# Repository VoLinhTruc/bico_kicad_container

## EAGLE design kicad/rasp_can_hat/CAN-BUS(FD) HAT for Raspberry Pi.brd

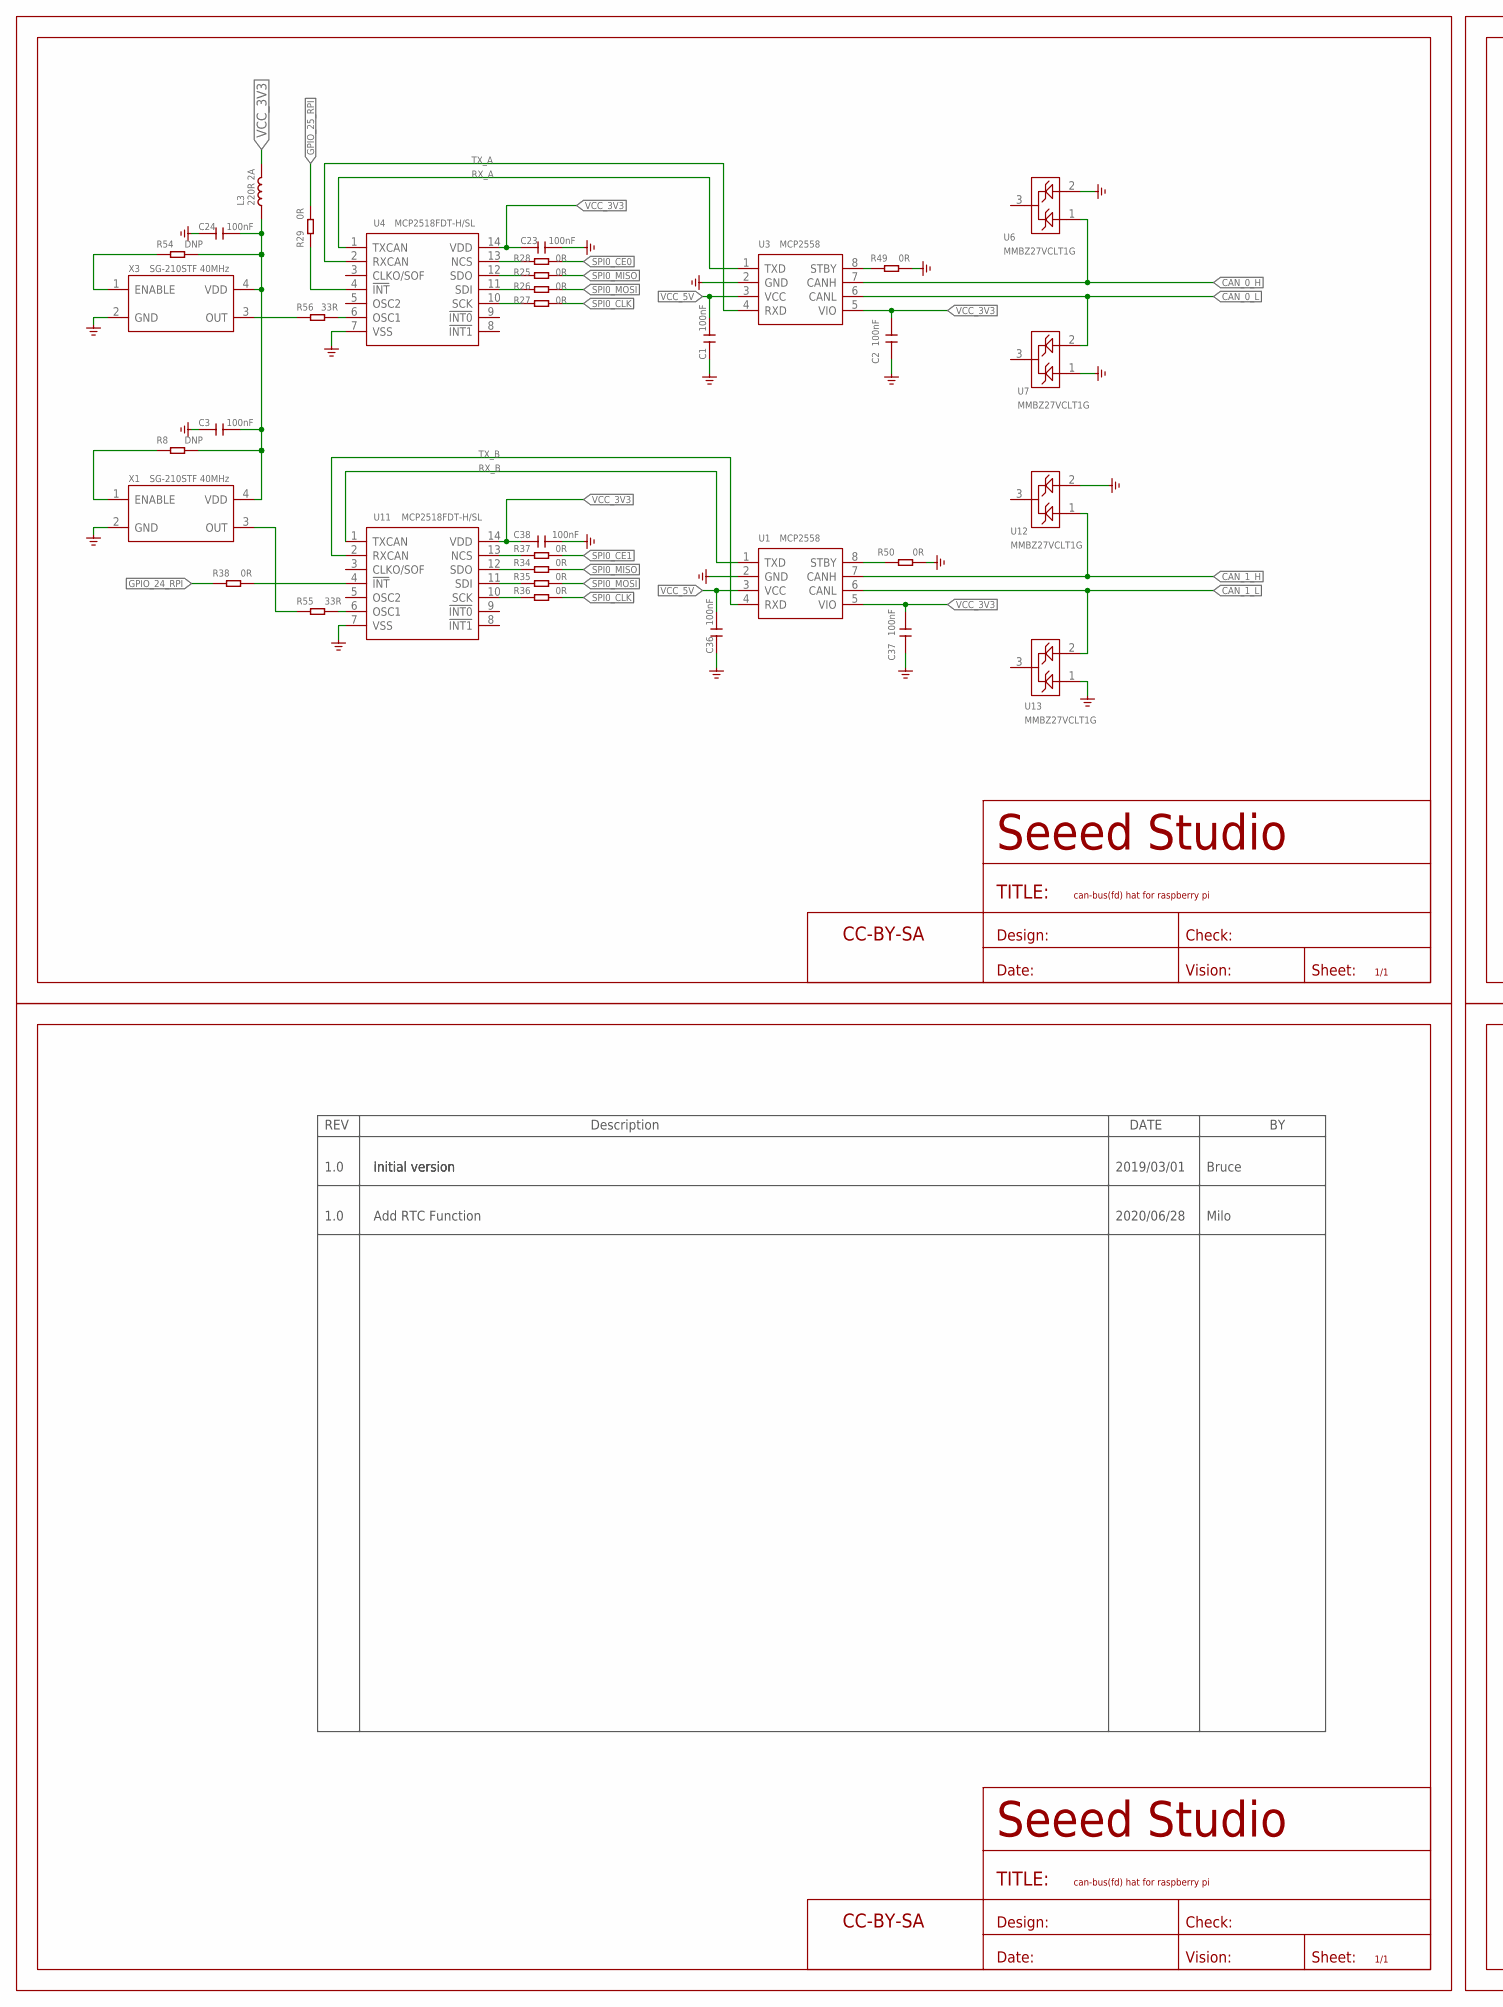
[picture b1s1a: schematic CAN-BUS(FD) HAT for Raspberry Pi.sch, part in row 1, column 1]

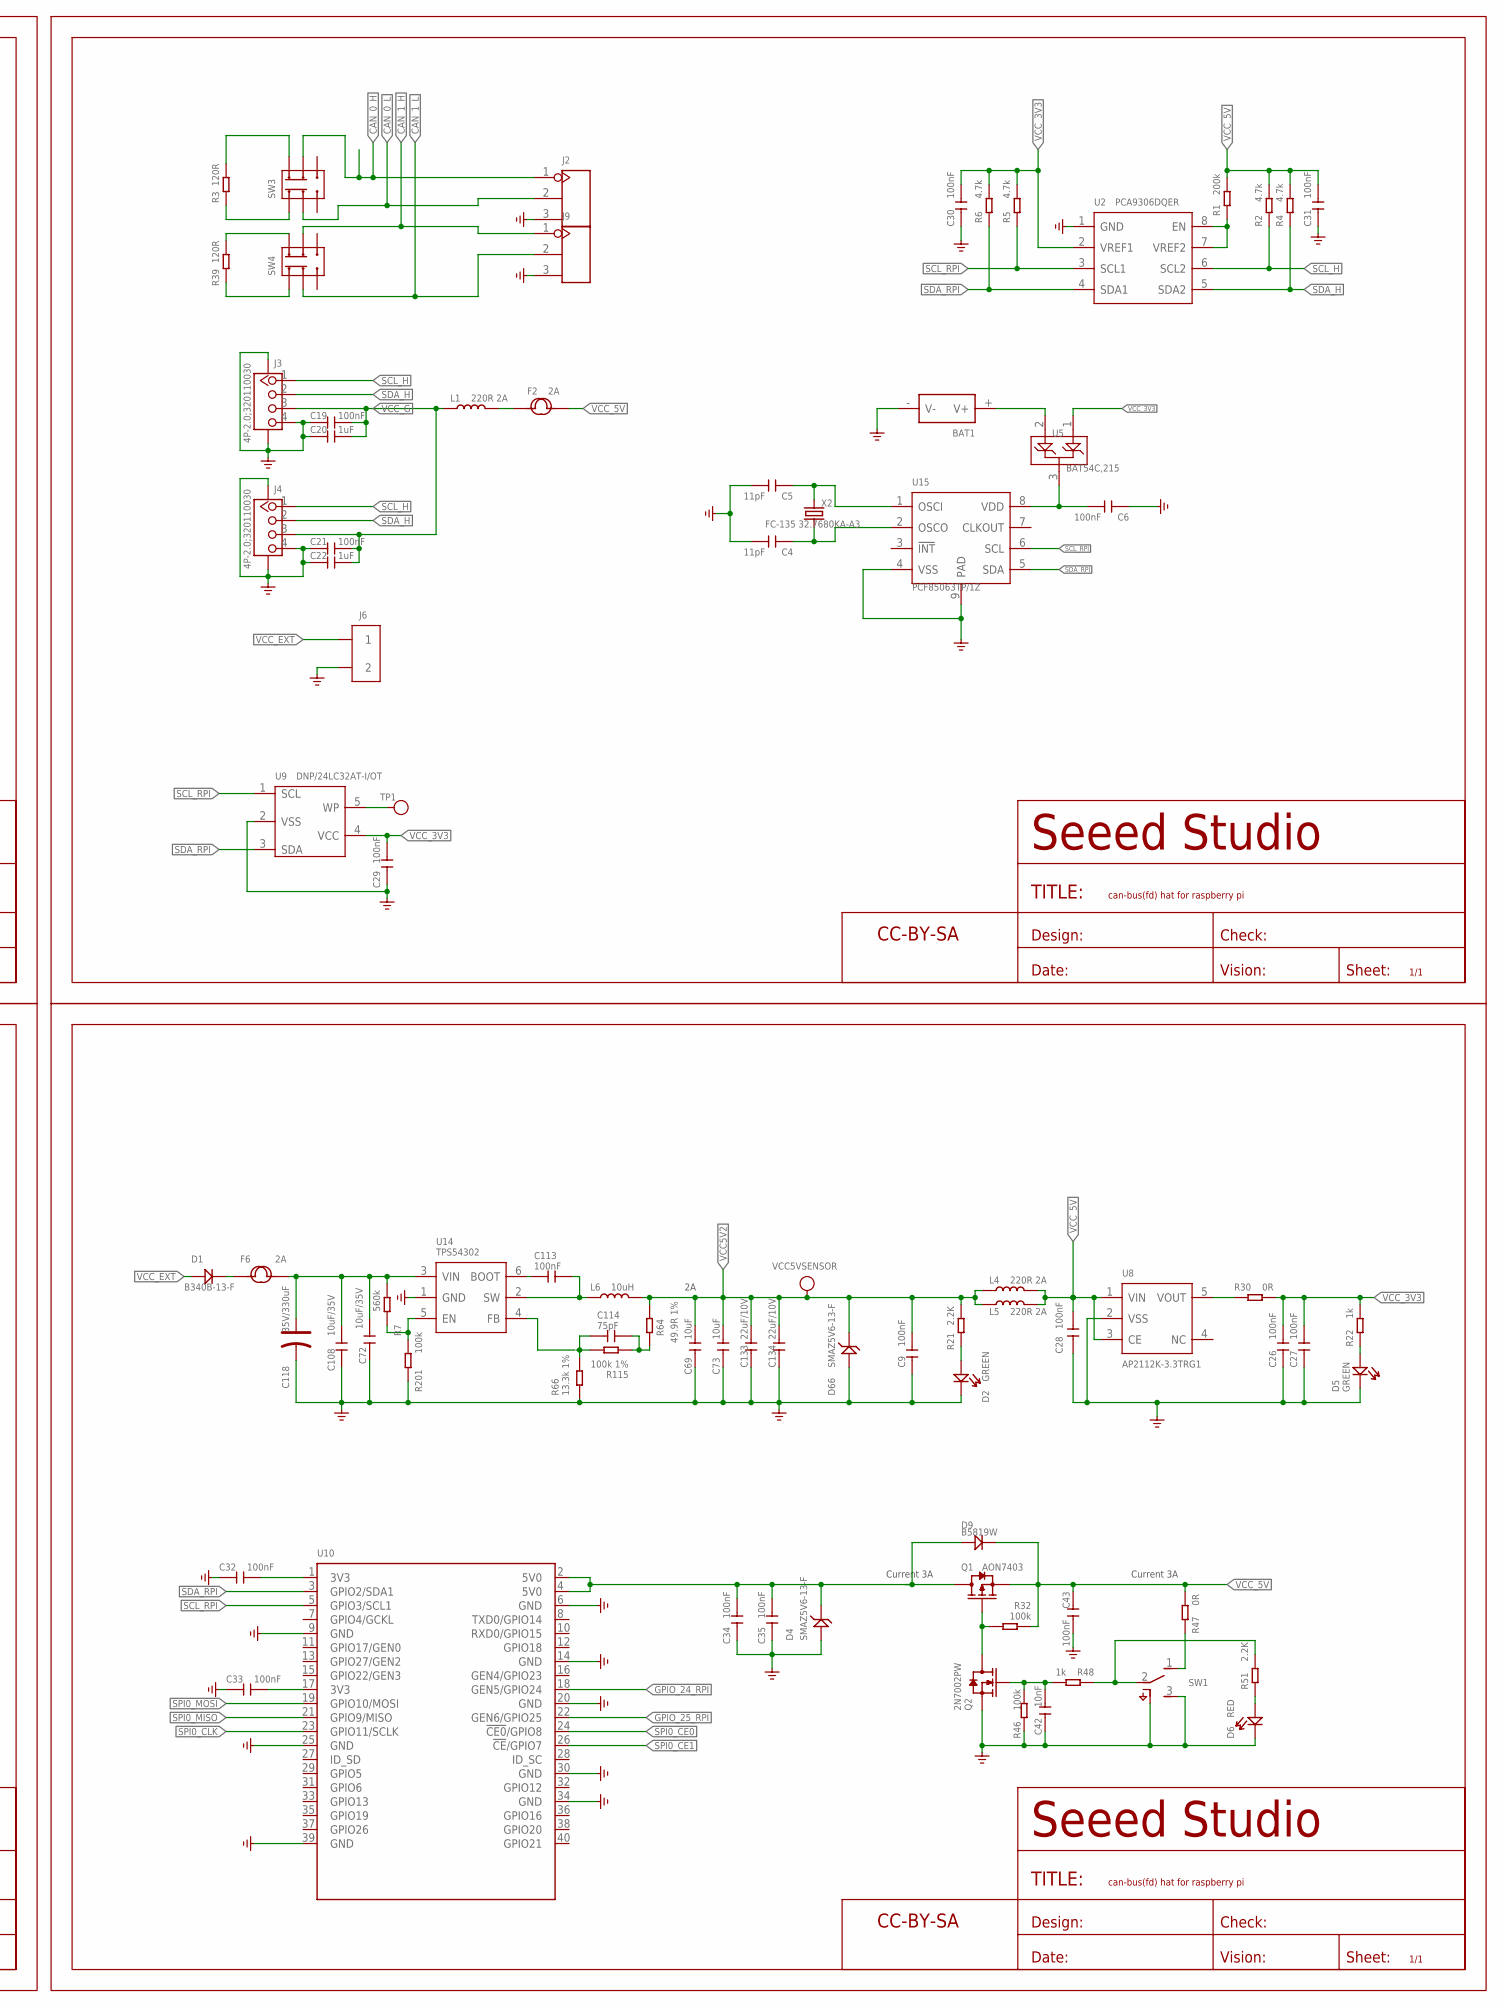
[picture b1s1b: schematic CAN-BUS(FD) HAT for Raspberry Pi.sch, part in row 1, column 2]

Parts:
BAT1: BAT-HOLDER'SMD-1220'; BAT2P-SMD-16.4-CR1220
C1, C2, C3, C6, C9, C19, C21, C23, C24, C26, C27, C28, C29, C30, C31, C32, C33, C34, C35, C36, C37, C38, C43, C113: 100nF; C0603
C4, C5: 11pF; C0603
C20, C22: 1uF; C0603
C42: 10nF; C0603
C69, C73: 10uF; C0805
C72, C108: 10uF/35V; C0805
C114: 75pF; C0603
C118: 35V/330uF; ELECTRO-SMD-E-7.8MM
C133, C134: 22uF/10V; C1206
D1: B340B-13-F; DO-214AA
D2, D5: GREEN; LED-0603
D4, D66: SMAZ5V6-13-F; DO-214AC
D6: RED; LED-0603
D9: B5819W; SOD-123
F2: 2A; FS1210
F6: 2A; F1812
FR1, FR2, FR3, FR5: SEEEDSTUDIO-OPEN-SCH-FRAME; SEEEDSTUDIO-PCB-FRAME
J2, J9: SCREW-TERMINAL-3P'3.5'; H3-3.5-11.5X7.0MM
J3, J4: 4P-2.0;320110030; HW4-SMD-2.0
J6: SCREW-TERMINAL-2P'3.5'; H2-3.5-7.0X7.0MM
L1, L3, L4, L5: 220R 2A; L0805
L6: 10uH; L8040
Q1: AON7403; DFN8P-0.65-3X3X0.8MM
Q2: 2N7002PW; SOT-23
R1: 200k; R0603
R2, R4, R5, R6: 4.7k; R0603
R3, R39: 120R; R1206
R7: 560k; R0603
R8, R54: DNP; 0603
R21, R51: 2.2K; 0603
R22, R48: 1k; 0603
R25, R26, R27, R28, R29, R34, R35, R36, R37, R38, R47, R49, R50: 0R; 0603
R30: 0R; R0603
R32, R46: 100k; 0603
R55, R56: 33R; 0603
R64: 49.9R 1%; R0603
R66: 13.3k 1%; R0603
R115: 100k 1%; R0603
R201: 100k; R0603
SW1: SWITCH-3+4P-311030001; SW7-SMD-L6.7X2.7X3.2MM
SW3, SW4: SWITCH-2CH-6P-311010004; SW6-2.54-9.0X3.5X3.2+2.0MM
TP1: DNP; TP-D45MIL
U1, U3: MCP2558; SOIC8-1.27-5X4MM
U2: PCA9306DQER; X2SON8-0.35-1.4X1X0.37MM
U4, U11: MCP2518FDT-H/SL; SOIC14-1.27-8.65X3.9MM
U5: BAT54C,215; SOT-23
U6, U7, U12, U13: MMBZ27VCLT1G; SOT-23
U8: AP2112K-3.3TRG1; SOT-25
U9: DNP/24LC32AT-I/OT; SOT-23-5
U10: RPI-ZERO-SMD/NP; H2X20-SMD/NP-2.54
U14: TPS54302; SOT-23-6
U15: PCF85063TP/1Z; HWSON8-0.5-2X3X0.75MM
VCC5VSENSOR: DNP; TP-D45MIL
X1, X3: SG-210STF 40MHz; X4-SMD-2.5X2.0X1.0MM
X2: FC-135 32.7680KA-A3; X2-SMD-3.2X1.5X0.55MM

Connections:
3V3@1: C32.1, U10.1 (3V3)
3V3@2: C33.1, U10.17 (3V3)
CAN_0_H: J2.1, SW3.COM2, U3.7 (CANH), U6.1
CAN_0_L: J2.2, SW3.COM1, U3.6 (CANL), U7.2
CAN_1_H: J9.1, SW4.COM2, U1.7 (CANH), U12.1
CAN_1_L: J9.2, SW4.COM1, U1.6 (CANL), U13.2
GND: BAT1.- (V-), C1.1, C2.1, C3.1, C4.1, C5.1, C6.2, C9.1, C19.1, C20.1, C21.1, C22.1, C23.1, C24.1, C26.1, C27.1, C28.1, C29.1, C30.2, C31.1, C32.2, C33.2, C34.2, C35.2, C36.1, C37.1, C38.1, C42.2, C43.2, C69.1, C72.1, C73.1, C108.1, C118.-, C133.1, C134.1, D2.-, D4.1 (+), D5.-, D6.-, D66.1 (+), J2.3, J3.4, J3.SS1, J3.SS2, J4.4, J4.SS1, J4.SS2, J6.2, J9.3, Q2.2 (S), R46.1, R49.2, R50.2, R66.1, R201.1, SW1.3 (B), SW1.SS1 (SS2), SW1.SS2, SW1.SS3 (SS2), SW1.SS4 (SS2), U1.2 (GND), U2.1 (GND), U3.2 (GND), U4.7 (VSS), U6.2, U7.1, U8.2 (VSS), U9.2 (VSS), U10.6 (GND), U10.9 (GND), U10.14 (GND), U10.20 (GND), U10.25 (GND), U10.30 (GND), U10.34 (GND), U10.39 (GND), U11.7 (VSS), U12.2, U13.1, U14.1 (GND), U15.4 (VSS), U15.9 (PAD), X1.2 (GND), X3.2 (GND)
GPIO_24_RPI: R38.2, U10.18 (GEN5/GPIO24)
GPIO_25_RPI: R29.2, U10.22 (GEN6/GPIO25)
unnamed: R47.1, SW1.1 (A)
unnamed: D1.2 (-), F6.1
unnamed: R55.1, U11.6 (OSC1)
unnamed: C114.2, R64.1, R115.1
unnamed: R55.2, X1.3 (OUT)
unnamed: R49.1, U3.8 (STBY)
unnamed: R7.1, R201.2, U14.5 (EN)
unnamed: R8.2, X1.1 (ENABLE)
unnamed: C3.2, C24.2, L3.1, R8.1, R54.1, X1.4 (VDD), X3.4 (VDD)
unnamed: R39.1, SW4.CH2A
unnamed: R56.2, X3.3 (OUT)
unnamed: R39.2, SW4.CH1A
unnamed: R29.1, U4.4 (!INT)
unnamed: R38.1, U11.4 (!INT)
unnamed: R50.1, U1.8 (STBY)
unnamed: R37.1, U11.13 (NCS)
unnamed: R3.1, SW3.CH2A
unnamed: R28.1, U4.13 (NCS)
unnamed: R25.1, U4.12 (SDO)
unnamed: R26.1, U4.11 (SDI)
unnamed: R27.1, U4.10 (SCK)
unnamed: R3.2, SW3.CH1A
unnamed: D5.+, R22.1
unnamed: C6.1, U5.3, U15.8 (VDD)
unnamed: R1.1, U2.7 (VREF2), U2.8 (EN)
unnamed: R34.1, U11.12 (SDO)
unnamed: BAT1.+ (V+), U5.2
unnamed: C4.2, U15.2 (OSCO), X2.1
unnamed: C5.2, U15.1 (OSCI), X2.2
unnamed: R35.1, U11.11 (SDI)
unnamed: R36.1, U11.10 (SCK)
unnamed: TP1.T, U9.5 (WP)
unnamed: R56.1, U4.6 (OSC1)
unnamed: D2.+, R21.1
unnamed: D6.+, R51.1
unnamed: C113.2, L6.1, U14.2 (SW)
unnamed: R30.1, U8.5 (VOUT)
unnamed: Q1.4 (G), Q2.3 (D), R32.2
unnamed: R48.1, R51.2, SW1.2 (COM)
unnamed: C42.1, Q2.1 (G), R46.2, R48.2
unnamed: F2.1, L1.2
unnamed: R54.2, X3.1 (ENABLE)
unnamed: C113.1, U14.6 (BOOT)
unnamed: C114.1, R66.2, R115.2, U14.4 (FB)
unnamed: C72.2, C108.2, C118.+, F6.2, R7.2, U14.3 (VIN)
RX_A: U3.1 (TXD), U4.1 (TXCAN)
RX_B: U1.1 (TXD), U11.1 (TXCAN)
SCL_H: J3.1, J4.1, R2.1, U2.6 (SCL2)
SCL_RPI: R5.1, U2.3 (SCL1), U9.1 (SCL), U10.5 (GPIO3/SCL1), U15.6 (SCL)
SDA_H: J3.2, J4.2, R4.1, U2.5 (SDA2)
SDA_RPI: R6.1, U2.4 (SDA1), U9.3 (SDA), U10.3 (GPIO2/SDA1), U15.5 (SDA)
SPI0_CE0: R28.2, U10.24 (!CE0!/GPIO8)
SPI0_CE1: R37.2, U10.26 (!CE!/GPIO7)
SPI0_CLK: R27.2, R36.2, U10.23 (GPIO11/SCLK)
SPI0_MISO: R25.2, R34.2, U10.21 (GPIO9/MISO)
SPI0_MOSI: R26.2, R35.2, U10.19 (GPIO10/MOSI)
TX_A: U3.4 (RXD), U4.2 (RXCAN)
TX_B: U1.4 (RXD), U11.2 (RXCAN)
VCC5V2: C9.2, C69.2, C73.2, C133.2, C134.2, D66.2 (-), L4.1, L5.1, L6.2, R21.2, R64.2, VCC5VSENSOR.T
VCC_3V3: C2.2, C23.2, C26.2, C27.2, C29.2, C30.1, C37.2, C38.2, L3.2, R5.2, R6.2, R22.2, R30.2, U1.5 (VIO), U2.2 (VREF1), U3.5 (VIO), U4.14 (VDD), U5.1, U9.4 (VCC), U11.14 (VDD)
VCC_5V: C1.2, C28.2, C31.2, C36.2, C43.1, D9.-, F2.2, L4.2, L5.2, Q1.1 (S), Q1.2 (S), Q1.3 (S), R1.2, R2.2, R4.2, R32.1, R47.2, U1.3 (VCC), U3.3 (VCC), U8.1 (VIN), U8.3 (CE)
VCC_5V_PI: C34.1, C35.1, D4.2 (-), D9.+, Q1.5 (D), Q1.6 (D), Q1.7 (D), Q1.8 (D), U10.2 (5V0), U10.4 (5V0)
VCC_EXT: D1.1 (+), J6.1
VCC_G: C19.2, C20.2, C21.2, C22.2, J3.3, J4.3, L1.1

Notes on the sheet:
Current 3A
1.0
initial version
Initial version
2019/03/01
Bruce
Add RTC Function
2020/06/28
Milo

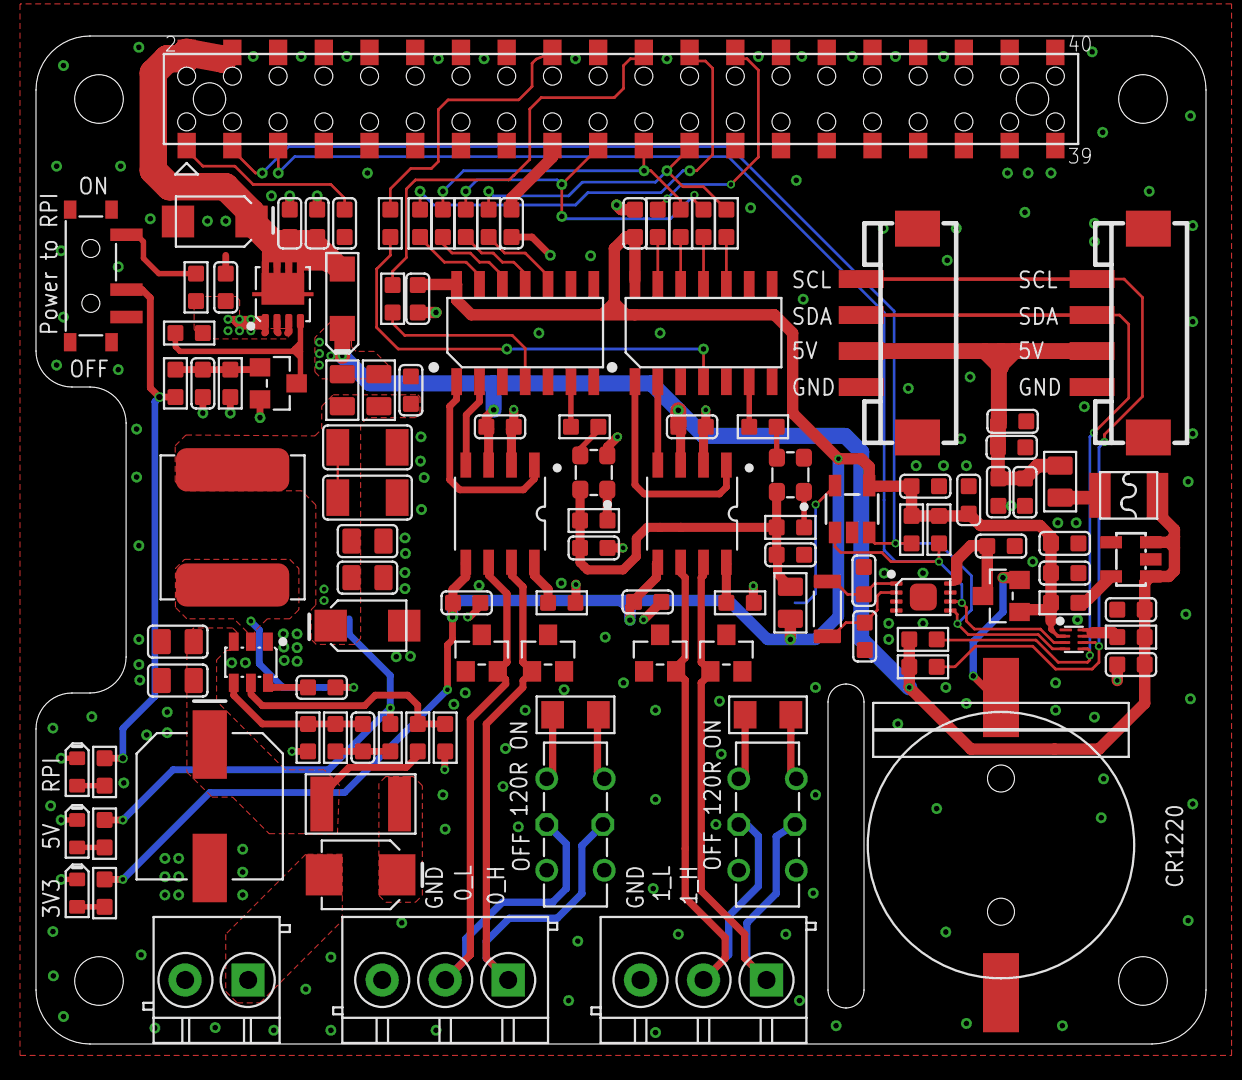
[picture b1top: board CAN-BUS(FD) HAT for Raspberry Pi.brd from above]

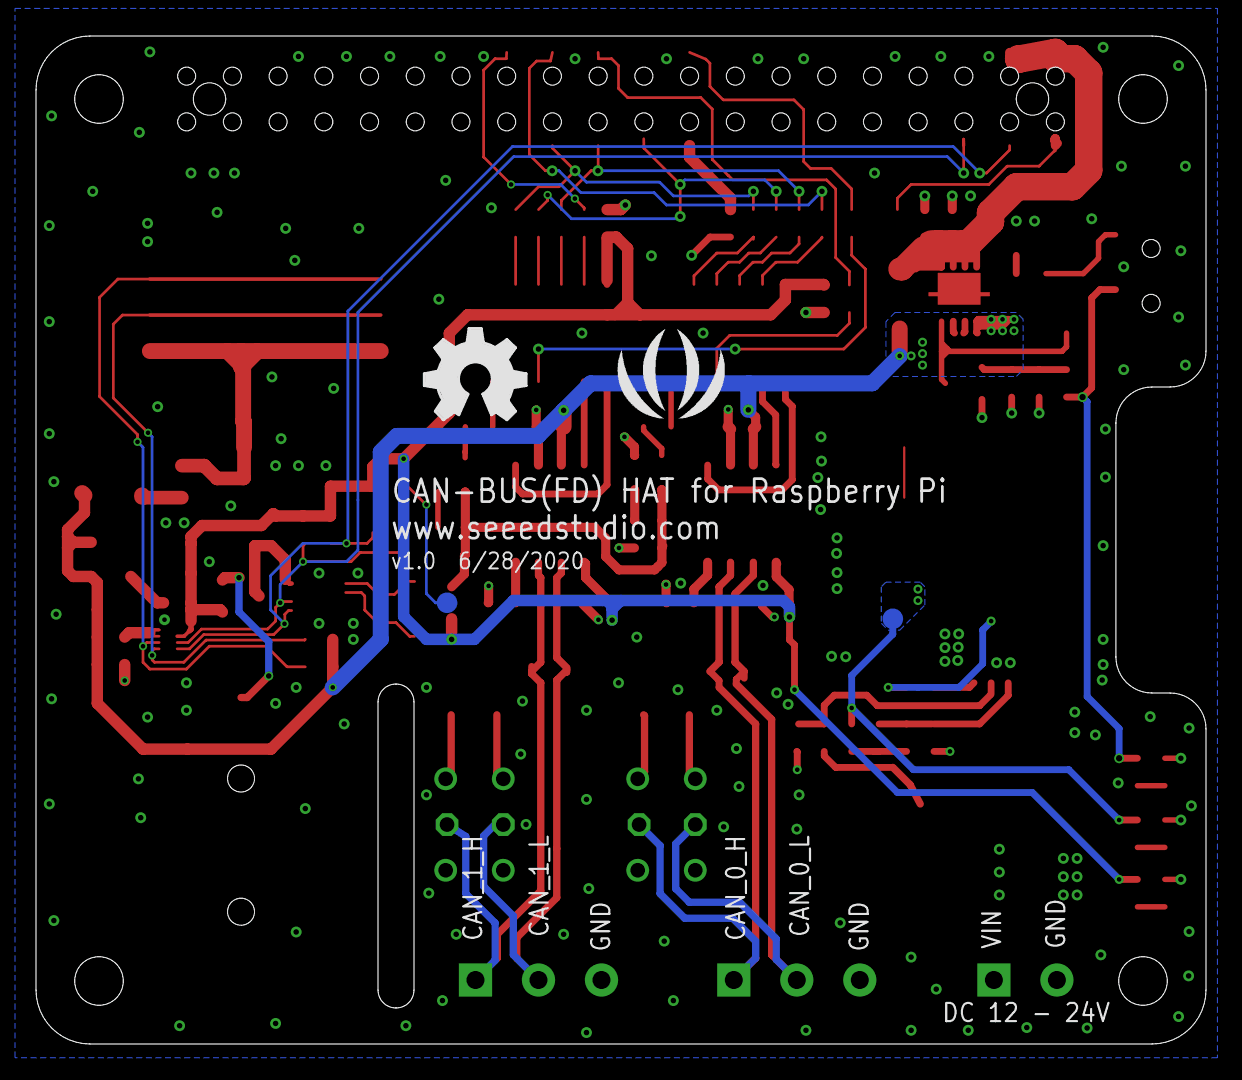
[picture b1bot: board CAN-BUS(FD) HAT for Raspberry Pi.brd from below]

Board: 2 copper layers, 65.0 x 56.0 mm, 124 parts (4 on the bottom side), 73 nets.

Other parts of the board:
U$42: OSHW_FILLX200_NOTEXT_TNAME
U$43: SEEED-SILK-TNAME-280*268MIL

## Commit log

2025-12-03 add kicad Uno shield project
2025-12-03 update to enable dark theme by default
2025-12-03 complete the hgt_lab_wiring, output in hgt_lab/hgt_lab/hgt_lab.svg
2025-12-03 comment out the dark theme setup, get back to KiCAD default theme. Reason: easier to color the schematic, in dark theme even the wrire colore set to green or red, what I see is dark red
2025-12-04 add annotation for hgt_lab schematic
2025-12-04 update schematic and generate the pdf file
2025-12-06 update docker file to clean cache -> reduce image size
2025-12-22 fix docker image build error
2025-12-22 update hgt_lab

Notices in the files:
parts and their libraries:
moudle-new: This work is licensed under the Creative Commons Attribution 4.0 International License.
To view a copy of this license,visit:
http://creativecommons.org/licenses/by-sa/4.0
moudle-new: CC-BY-SA
